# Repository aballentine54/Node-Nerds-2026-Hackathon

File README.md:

# The Project:  
### - a video game-esque compass that sends you to one of 5 selected locations - or geocaches - on campus.  
### - made with an Arduino Uno, two potentiometers, a GPS chip, an lcd screen, hopes, & dreams.  

# The Nerds:
Autumn Hazel - hazel.11@wright.edu  
Andrew Ballentine - ballentine.8@wright.edu  
Kwaku Nhyira Sefa-Badu - Sefa-badu.2@wright.edu  
Michael Gott - Gott.7@wright.edu  
Tommy Dinh Khoi Nguyen Le - le.91@wright.edu

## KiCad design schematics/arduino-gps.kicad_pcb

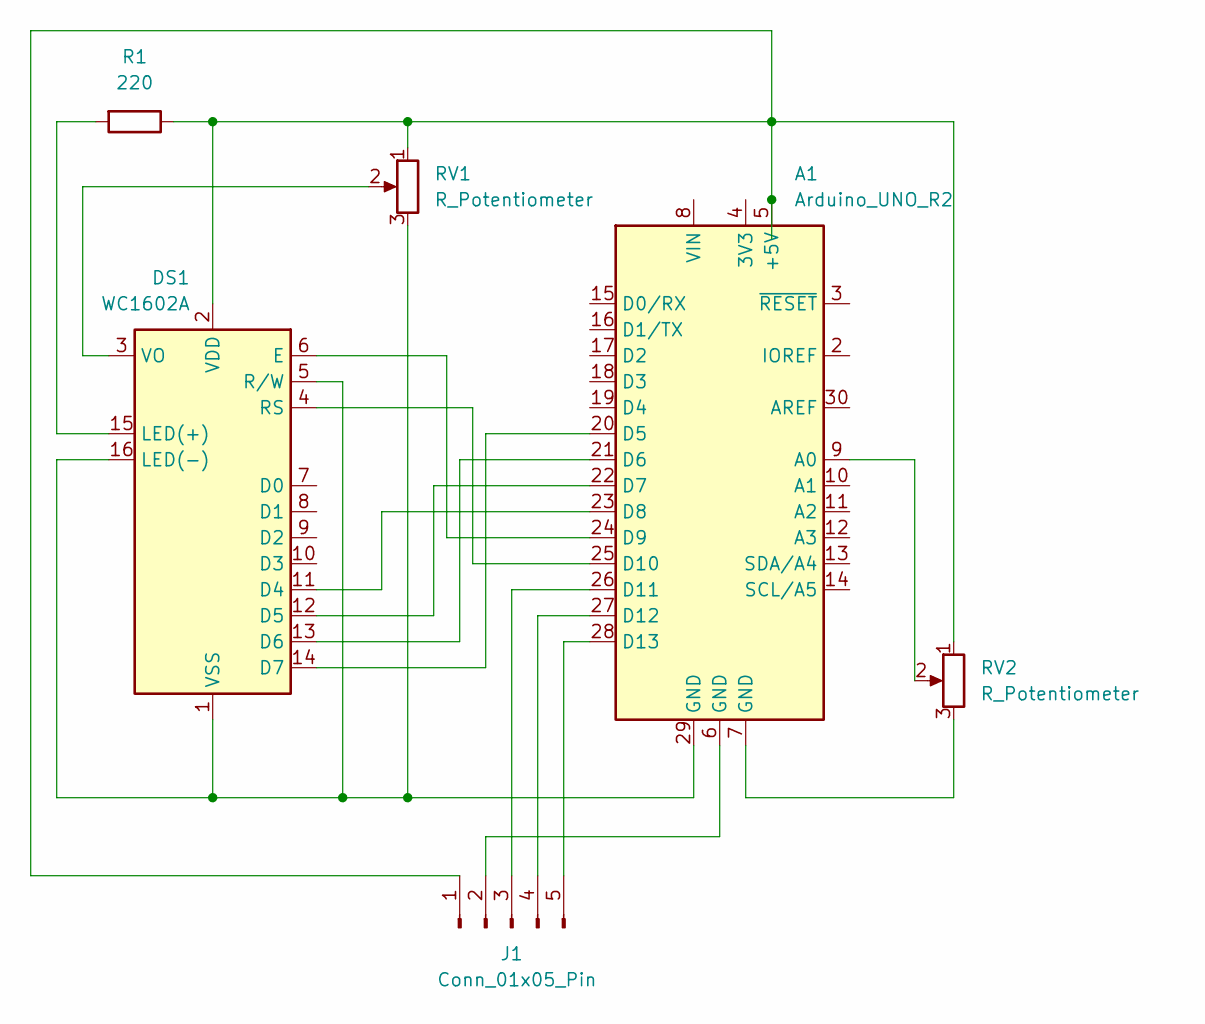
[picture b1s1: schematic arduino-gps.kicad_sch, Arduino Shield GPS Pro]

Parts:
A1: Arduino_UNO_R2
DS1: WC1602A
J1: Conn_01x05_Pin; JST_EH_B5B-EH-A_1x05_P2.50mm_Vertical
R1: 220; R_Axial_DIN0204_L3.6mm_D1.6mm_P5.08mm_Vertical
RV1, RV2: R_Potentiometer; Potentiometer_ACP_CA9-V10_Vertical

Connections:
unnamed: A1.5 (+5V), DS1.2 (VDD), J1.1, R1.1, RV1.1, RV2.1
unnamed: A1.9 (A0), RV2.2
unnamed: A1.20 (D5), DS1.14 (D7)
unnamed: A1.21 (D6), DS1.13 (D6)
unnamed: A1.22 (D7), DS1.12 (D5)
unnamed: A1.23 (D8), DS1.11 (D4)
unnamed: A1.24 (D9), DS1.6 (E)
unnamed: A1.25 (D10), DS1.4 (RS)
unnamed: A1.26 (D11), J1.3
unnamed: A1.27 (D12), J1.4
unnamed: A1.28 (D13), J1.5
unnamed: A1.7 (GND), RV2.3
unnamed: DS1.15 (LED(+)), R1.2
unnamed: A1.29 (GND), DS1.1 (VSS), DS1.5 (R/W), DS1.16 (LED(-)), RV1.3
unnamed: DS1.3 (VO), RV1.2
unnamed: A1.6 (GND), J1.2

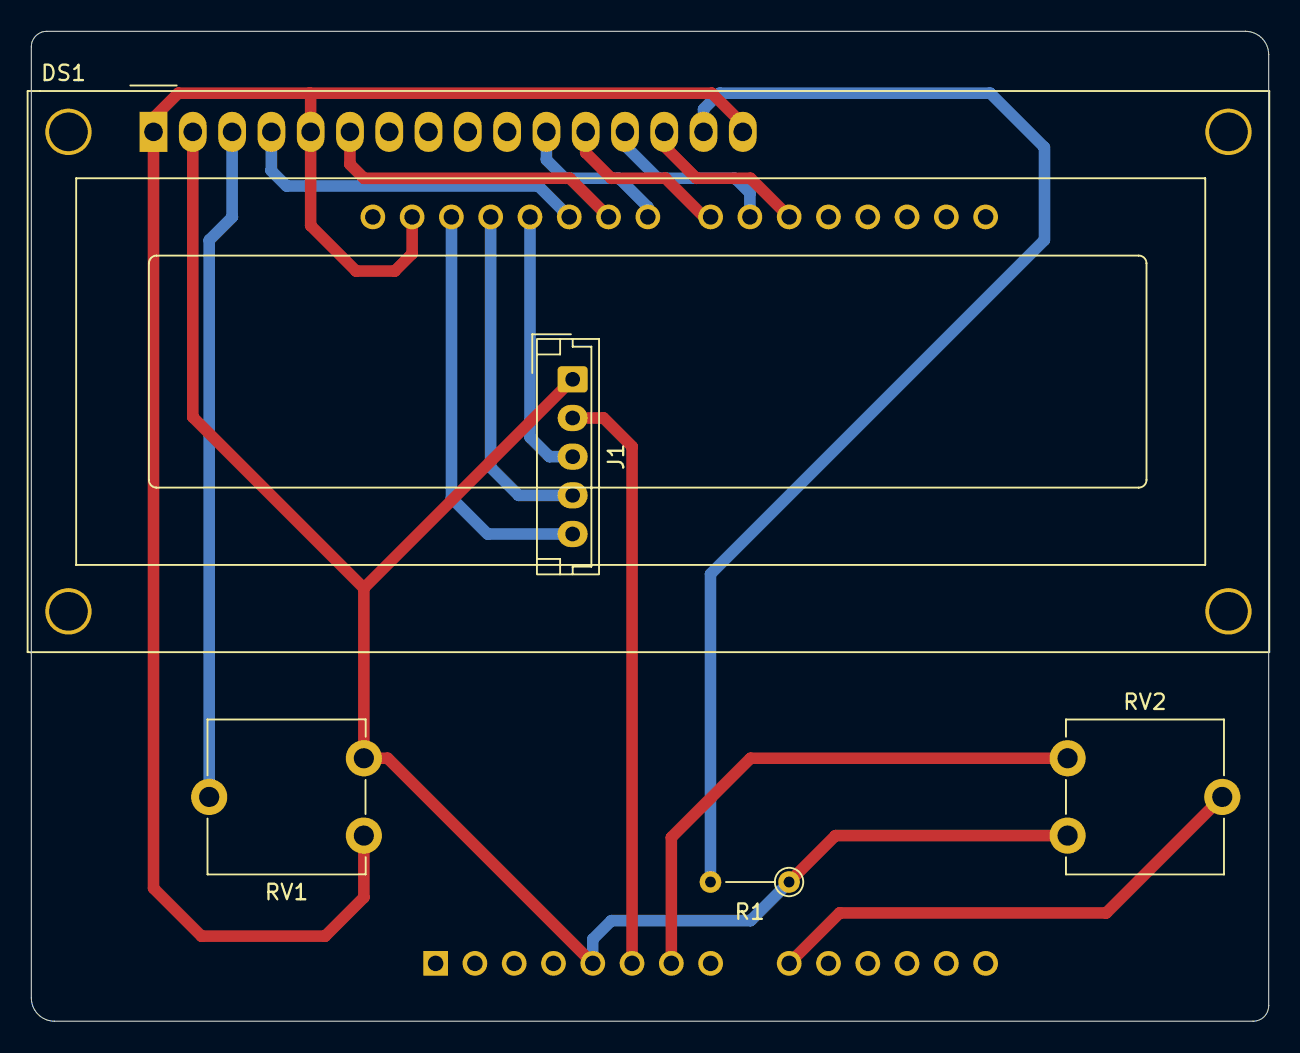
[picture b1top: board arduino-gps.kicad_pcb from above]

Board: 2 copper layers, 80.0 x 64.0 mm, 6 parts (1 on the bottom side), 16 nets.

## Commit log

2026-02-06 added roster - need full names
2026-02-07 Kwaku + Tommy gps code
2026-02-07 Add files via upload
    i added the double arrows, to account for the intermediate cardinal points. e.g. NW,SE,SW and NE
2026-02-07 Uploading unoR2 schematics
2026-02-07 Polished arduino code
2026-02-07 missed a few optimizations last commit
2026-02-07 added documentation
2026-02-07 Clear previous LCD message before displaying new text
2026-02-09 updating with emails
2026-02-11 Updated README.md with team emails
